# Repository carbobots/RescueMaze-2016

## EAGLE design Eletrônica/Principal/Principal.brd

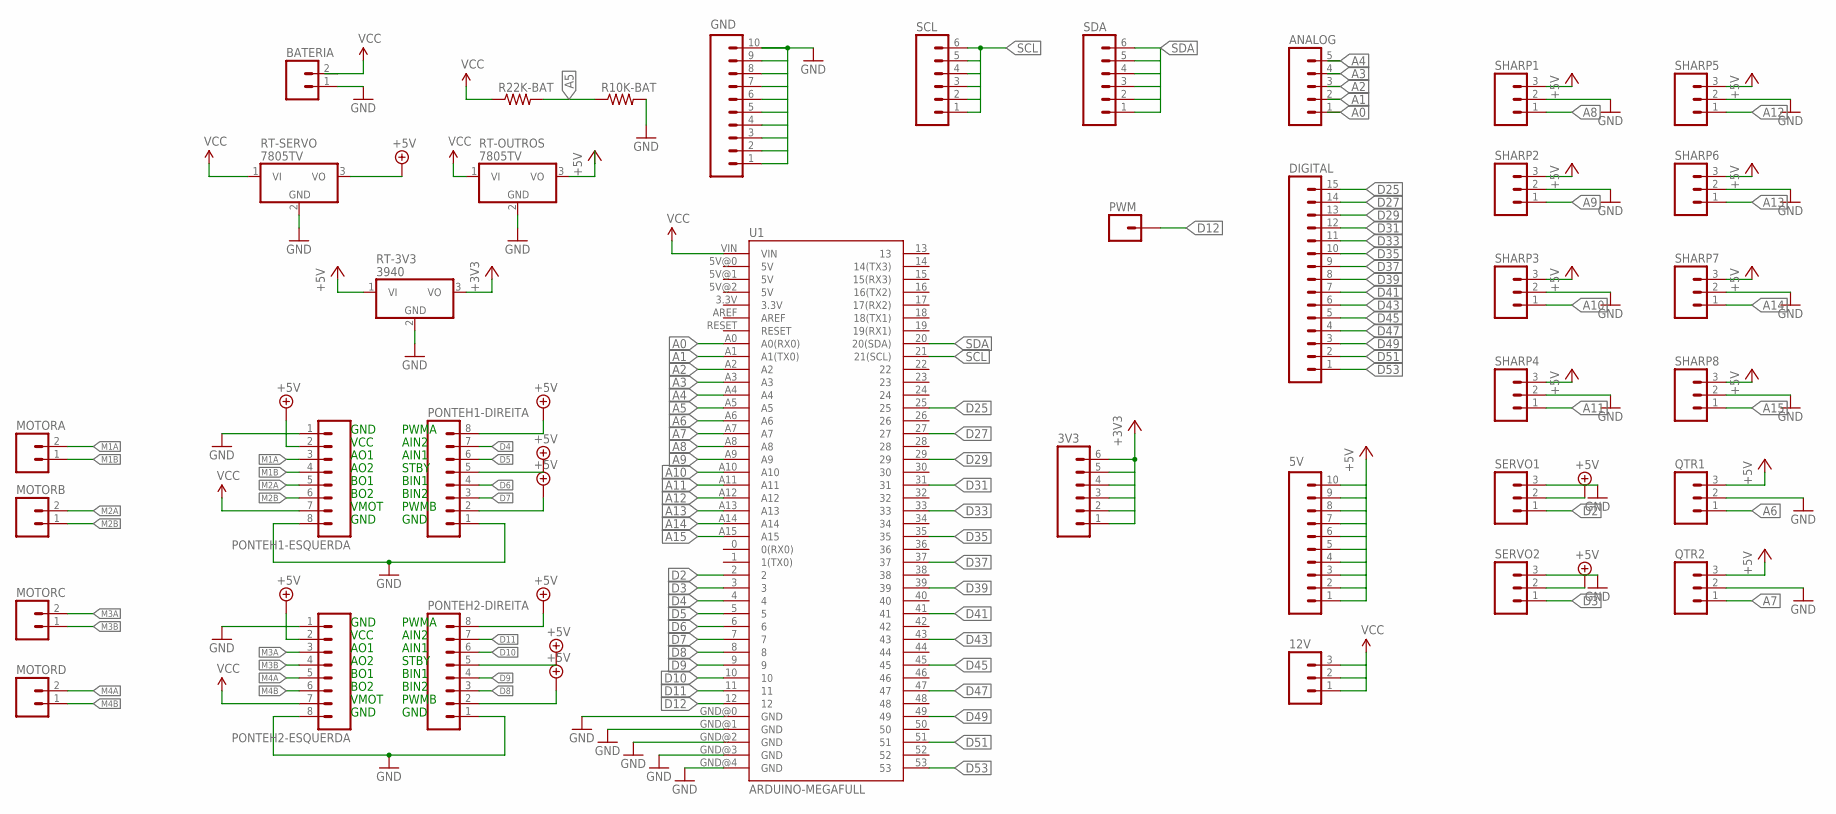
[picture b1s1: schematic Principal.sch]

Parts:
3V3: M06SILK_FEMALE_PTH; 1X06
5V: M10SILK_FEMALE_PTH; 1X10
12V: M03PTH; 1X03
ANALOG: M05PTH; 1X05
BATERIA: M02PTH; 1X02
DIGITAL: M15; 1X15
GND: M10SILK_FEMALE_PTH; 1X10
MOTORA: M02PTH; 1X02
MOTORB: M02PTH; 1X02
MOTORC: M02PTH; 1X02
MOTORD: M02PTH; 1X02
PONTEH1-DIREITA, PONTEH1-ESQUERDA, PONTEH2-DIREITA, PONTEH2-ESQUERDA: M08; 1X08_ROUND
PWM: M01PTH; 1X01
QTR1, QTR2: M03PTH; 1X03
R10K-BAT, R22K-BAT: RESISTORPTH-1/4W; AXIAL-0.4
RT-3V3: 3940; TO220V
RT-OUTROS: 7805TV; TO220V
RT-SERVO: 7805TV; TO220V
SCL: M06SILK_FEMALE_PTH; 1X06
SDA: M06SILK_FEMALE_PTH; 1X06
SERVO1, SERVO2: M03PTH; 1X03
SHARP1, SHARP2, SHARP3, SHARP4, SHARP5, SHARP6, SHARP7, SHARP8: M03PTH; 1X03
U1: ARDUINO-MEGAFULL; ARDUINO_MEGA

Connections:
3V3: 3V3.2, 3V3.3, 3V3.4, 3V3.5, RT-3V3.3 (VO)
5V: 5V.2, 5V.3, 5V.4, 5V.5, 5V.6, 5V.7, 5V.8, 5V.9, 5V.10, RT-OUTROS.3 (VO)
+3V3: 3V3.1, 3V3.6
+5V: 5V.1, PONTEH1-DIREITA.2, PONTEH1-DIREITA.5, PONTEH1-DIREITA.8, PONTEH1-ESQUERDA.2, PONTEH2-DIREITA.2, PONTEH2-DIREITA.5, PONTEH2-DIREITA.8, PONTEH2-ESQUERDA.2, QTR1.3, QTR2.3, RT-3V3.1 (VI), RT-SERVO.3 (VO), SERVO1.2, SERVO2.2, SHARP1.3, SHARP2.3, SHARP3.3, SHARP4.3, SHARP5.3, SHARP6.3, SHARP7.3, SHARP8.3
A0: ANALOG.1, U1.A0 (A0(RX0))
A1: ANALOG.2, U1.A1 (A1(TX0))
A2: ANALOG.3, U1.A2
A3: ANALOG.4, U1.A3
A4: ANALOG.5, U1.A4
A5: R10K-BAT.P$1 (1), R22K-BAT.P$2 (2), U1.A5
A6: QTR1.1, U1.A6
A7: QTR2.1, U1.A7
A8: SHARP1.1, U1.A8
A9: SHARP2.1, U1.A9
A10: SHARP3.1, U1.A10
A11: SHARP4.1, U1.A11
A12: SHARP5.1, U1.A12
A13: SHARP6.1, U1.A13
A14: SHARP7.1, U1.A14
A15: SHARP8.1, U1.A15
D2: SERVO1.1, U1.2
D3: SERVO2.1, U1.3
D4: PONTEH1-DIREITA.7, U1.4
D5: PONTEH1-DIREITA.6, U1.5
D6: PONTEH1-DIREITA.4, U1.6
D7: PONTEH1-DIREITA.3, U1.7
D8: PONTEH2-DIREITA.3, U1.8
D9: PONTEH2-DIREITA.4, U1.9
D10: PONTEH2-DIREITA.6, U1.10
D11: PONTEH2-DIREITA.7, U1.11
D12: PWM.1, U1.12
D25: DIGITAL.15, U1.25
D27: DIGITAL.14, U1.27
D29: DIGITAL.13, U1.29
D31: DIGITAL.12, U1.31
D33: DIGITAL.11, U1.33
D35: DIGITAL.10, U1.35
D37: DIGITAL.9, U1.37
D39: DIGITAL.8, U1.39
D41: DIGITAL.7, U1.41
D43: DIGITAL.6, U1.43
D45: DIGITAL.5, U1.45
D47: DIGITAL.4, U1.47
D49: DIGITAL.3, U1.49
D51: DIGITAL.2, U1.51
D53: DIGITAL.1, U1.53
GND: BATERIA.1, GND.1, GND.10, PONTEH1-DIREITA.1, PONTEH1-ESQUERDA.1, PONTEH1-ESQUERDA.8, PONTEH2-DIREITA.1, PONTEH2-ESQUERDA.1, PONTEH2-ESQUERDA.8, QTR1.2, QTR2.2, R10K-BAT.P$2 (2), RT-3V3.2 (GND), RT-OUTROS.2 (GND), RT-SERVO.2 (GND), SERVO1.3, SERVO2.3, SHARP1.2, SHARP2.2, SHARP3.2, SHARP4.2, SHARP5.2, SHARP6.2, SHARP7.2, SHARP8.2, U1.GND@0 (GND), U1.GND@1 (GND), U1.GND@2 (GND), U1.GND@3 (GND), U1.GND@4 (GND)
M1A: MOTORA.2, PONTEH1-ESQUERDA.3
M1B: MOTORA.1, PONTEH1-ESQUERDA.4
M2A: MOTORB.2, PONTEH1-ESQUERDA.5
M2B: MOTORB.1, PONTEH1-ESQUERDA.6
M3A: MOTORC.2, PONTEH2-ESQUERDA.3
M3B: MOTORC.1, PONTEH2-ESQUERDA.4
M4A: MOTORD.2, PONTEH2-ESQUERDA.5
M4B: MOTORD.1, PONTEH2-ESQUERDA.6
SCL: SCL.1, SCL.2, SCL.3, SCL.4, SCL.5, SCL.6, U1.21 (21(SCL))
SDA: SDA.1, SDA.2, SDA.3, SDA.4, SDA.5, SDA.6, U1.20 (20(SDA))
VCC: 12V.1, 12V.2, 12V.3, BATERIA.2, PONTEH1-ESQUERDA.7, PONTEH2-ESQUERDA.7, R22K-BAT.P$1 (1), RT-OUTROS.1 (VI), RT-SERVO.1 (VI), U1.VIN

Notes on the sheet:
GND
VCC
AO1
AO2
BO1
BO2
VMOT
PWMA
AIN2
AIN1
STBY
BIN1
BIN2
PWMB

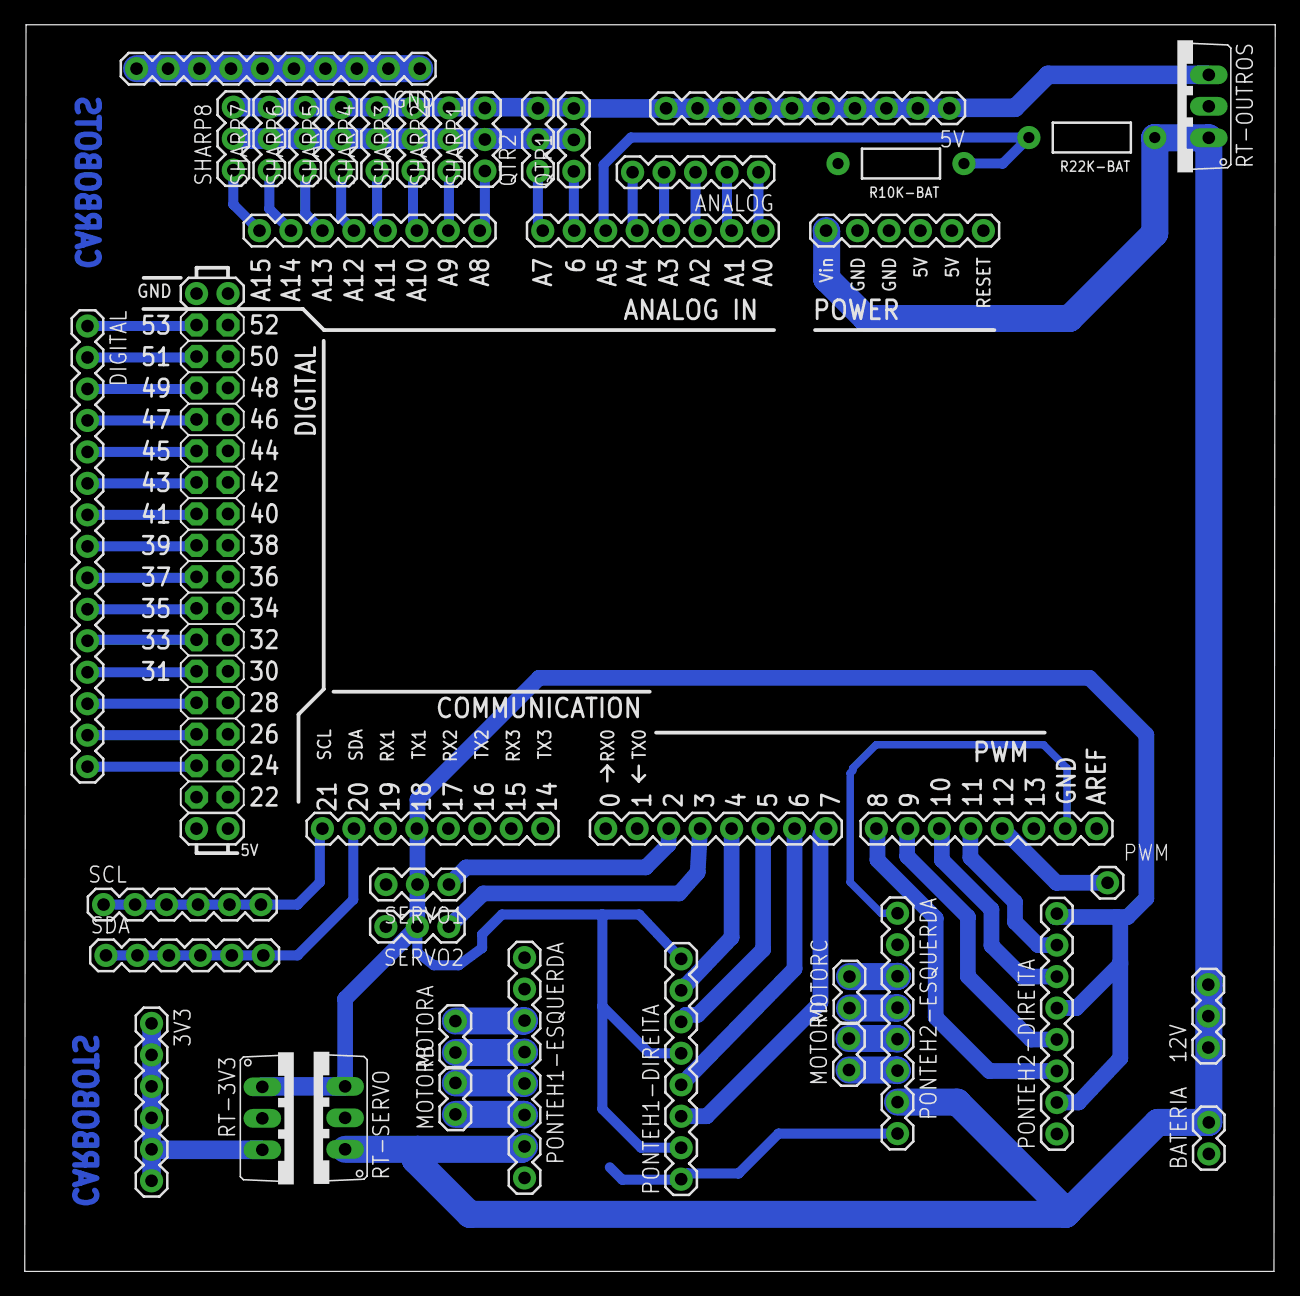
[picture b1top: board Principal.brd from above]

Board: 2 copper layers, 100.9 x 100.6 mm, 36 parts (0 on the bottom side), 58 nets.

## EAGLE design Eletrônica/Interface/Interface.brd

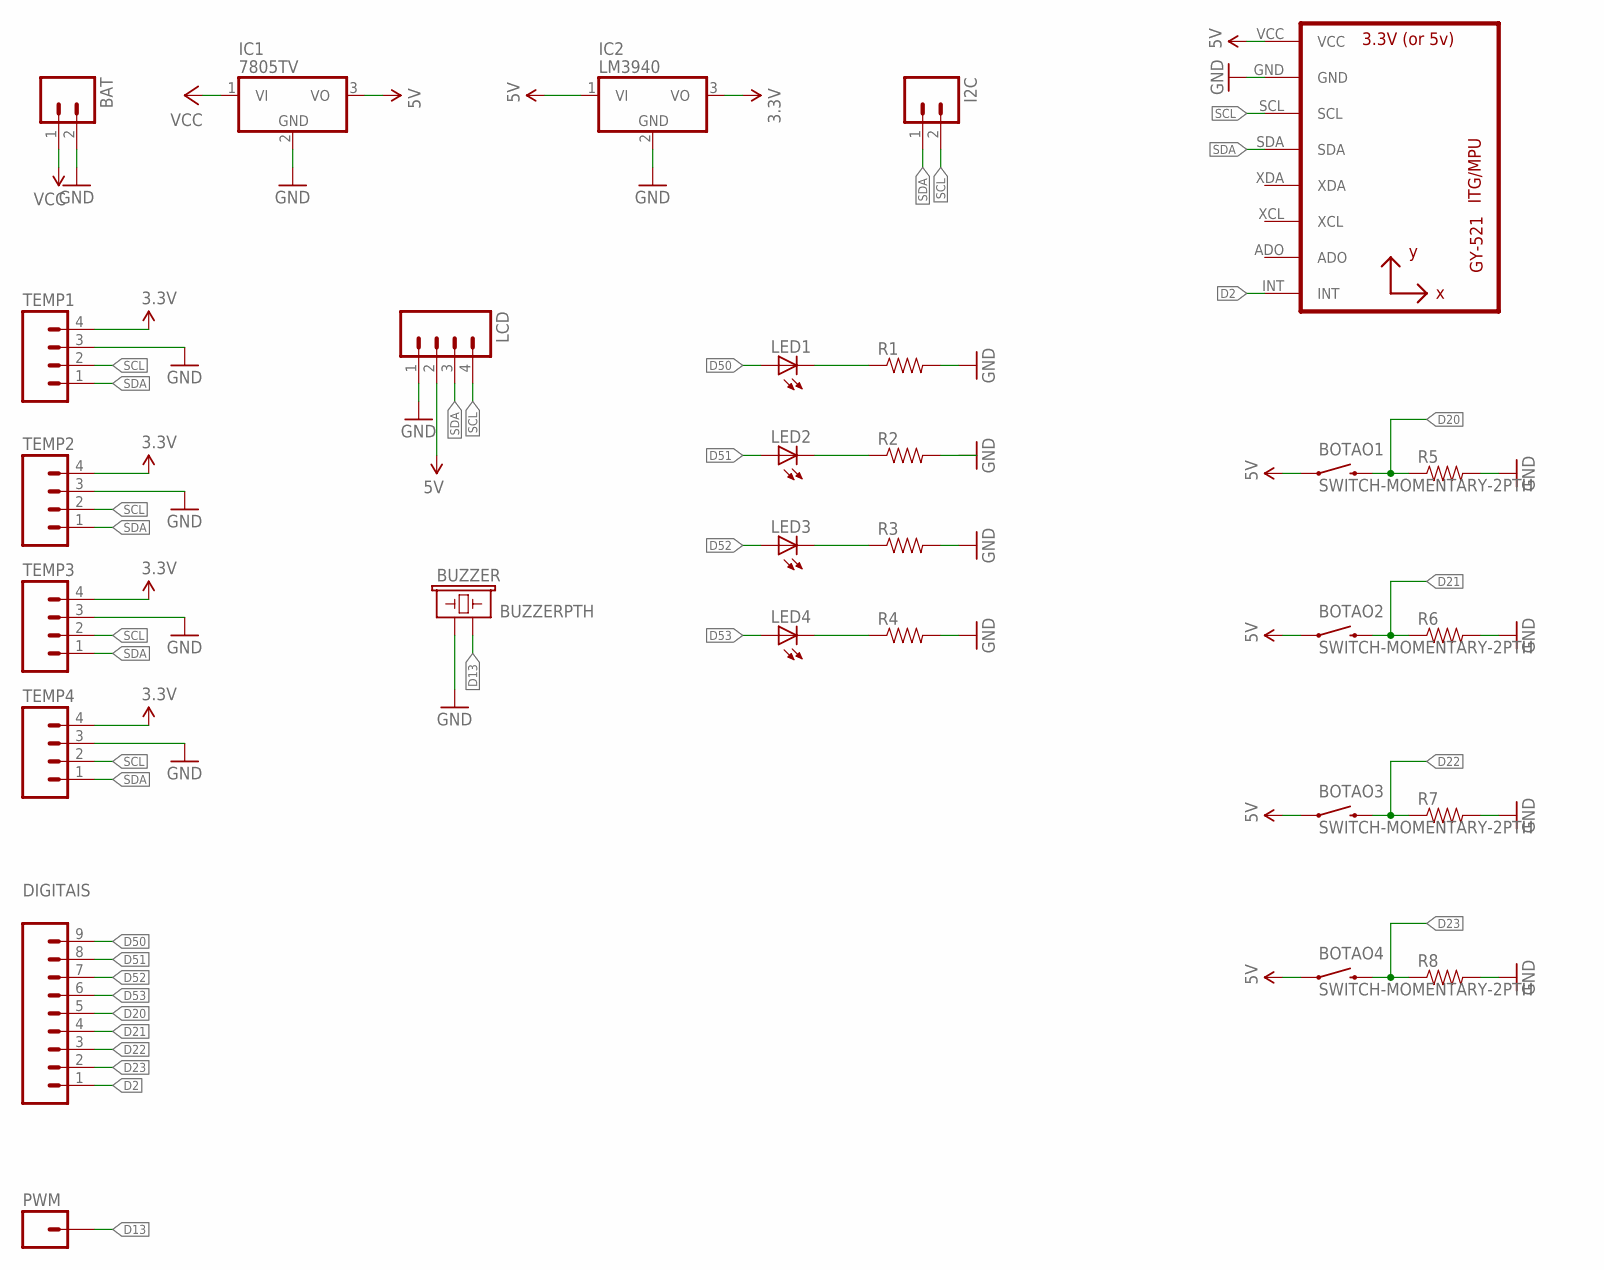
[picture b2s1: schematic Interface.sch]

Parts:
BAT: M02PTH; 1X02
BOTAO1, BOTAO2, BOTAO3, BOTAO4: SWITCH-MOMENTARY-2PTH; TACTILE-PTH
BUZZER: BUZZERPTH; BUZZER-12MM
DIGITAIS: M09; 1X09
I2C: M02PTH; 1X02
IC1: 7805TV; TO220V
IC2: LM3940; TO220V
LCD: M04PTH; 1X04
LED1, LED2, LED3, LED4: LED5MM
PWM: M01PTH; 1X01
R1, R2, R3, R4, R5, R6, R7, R8: RESISTOREZ; AXIAL-0.3EZ
TEMP1, TEMP2, TEMP3, TEMP4: M04PTH; 1X04
U1: GY-521MPU6050; GY-521

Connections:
3.3V: IC2.3 (VO), TEMP1.4, TEMP2.4, TEMP3.4, TEMP4.4
5V: BOTAO1.1, BOTAO2.1, BOTAO3.1, BOTAO4.1, IC1.3 (VO), IC2.1 (VI), LCD.2, U1.VCC
D2: DIGITAIS.1, U1.INT
D13: BUZZER.- (2), PWM.1
D20: BOTAO1.3 (2), DIGITAIS.5, R5.P$1 (1)
D21: BOTAO2.3 (2), DIGITAIS.4, R6.P$1 (1)
D22: BOTAO3.3 (2), DIGITAIS.3, R7.P$1 (1)
D23: BOTAO4.3 (2), DIGITAIS.2, R8.P$1 (1)
D50: DIGITAIS.9, LED1.A
D51: DIGITAIS.8, LED2.A
D52: DIGITAIS.7, LED3.A
D53: DIGITAIS.6, LED4.A
GND: BAT.2, BUZZER.+ (1), IC1.2 (GND), IC2.2 (GND), LCD.1, R1.P$2 (2), R2.P$2 (2), R3.P$2 (2), R4.P$2 (2), R5.P$2 (2), R6.P$2 (2), R7.P$2 (2), R8.P$2 (2), TEMP1.3, TEMP2.3, TEMP3.3, TEMP4.3, U1.GND
unnamed: LED3.K (C), R3.P$1 (1)
unnamed: LED1.K (C), R1.P$1 (1)
unnamed: LED2.K (C), R2.P$1 (1)
unnamed: LED4.K (C), R4.P$1 (1)
SCL: I2C.2, LCD.4, TEMP1.2, TEMP2.2, TEMP3.2, TEMP4.2, U1.SCL
SDA: I2C.1, LCD.3, TEMP1.1, TEMP2.1, TEMP3.1, TEMP4.1, U1.SDA
VCC: BAT.1, IC1.1 (VI)

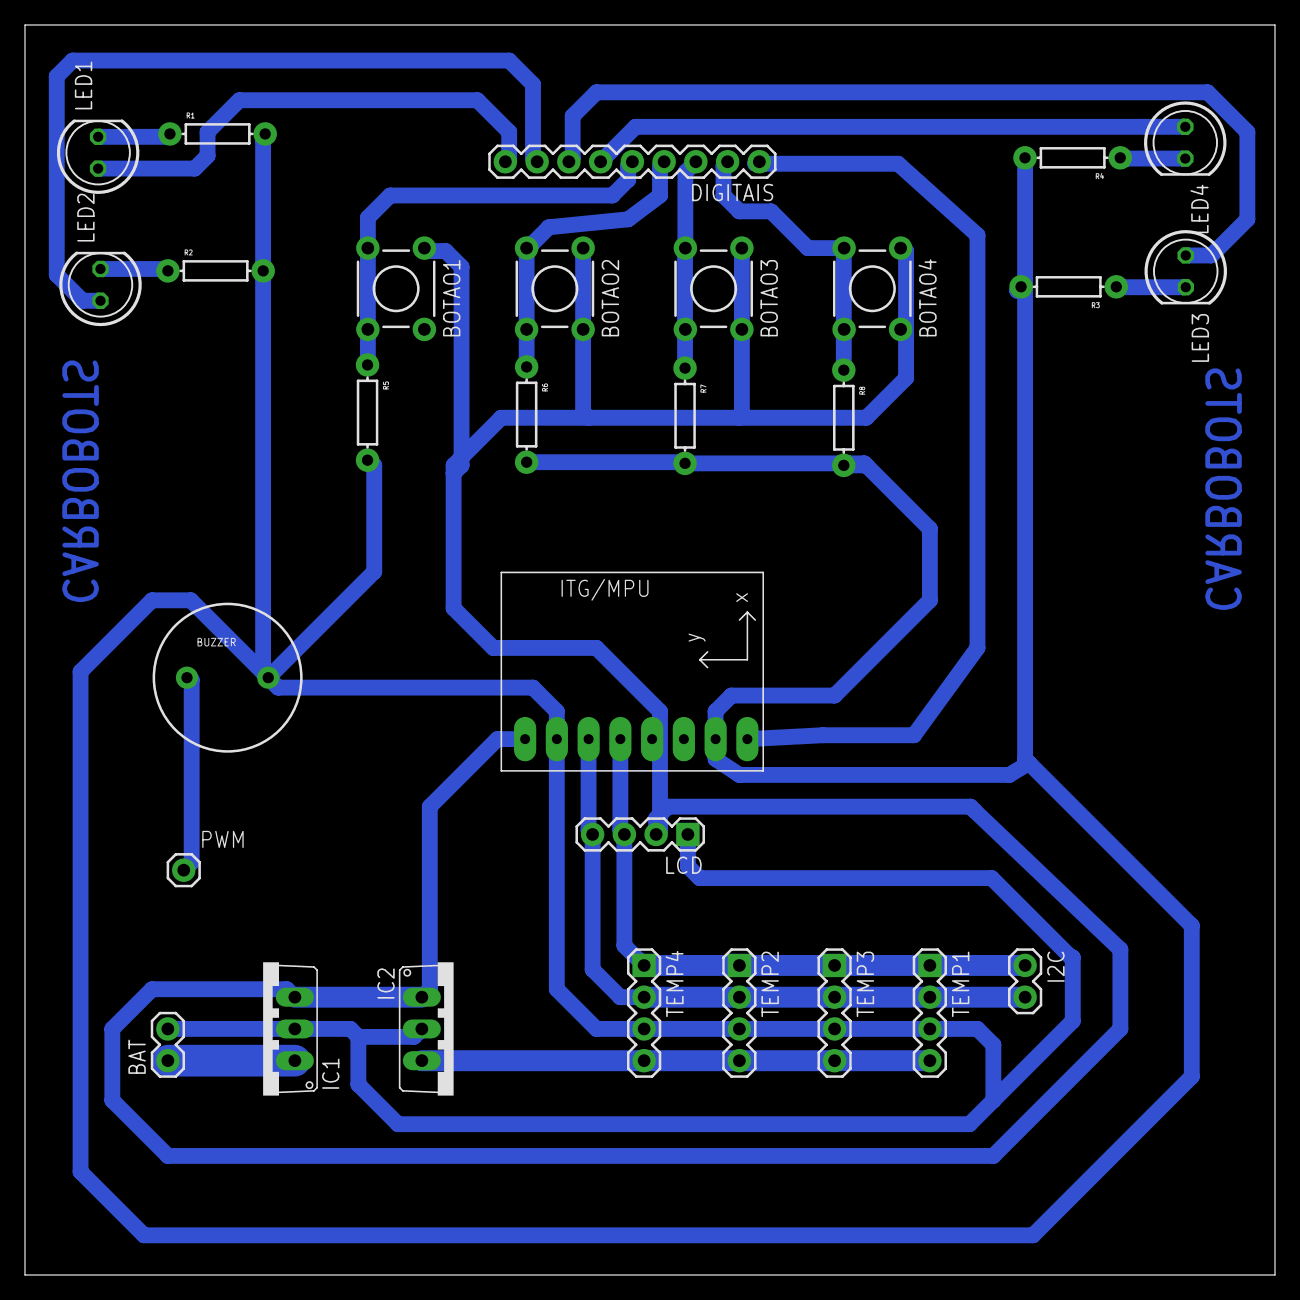
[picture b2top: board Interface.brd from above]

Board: 2 copper layers, 100.0 x 100.0 mm, 29 parts (0 on the bottom side), 20 nets.

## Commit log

2017-05-22 Rescue Maze 2016

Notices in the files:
parts and their libraries:
SparkFun-Connectors: Licensing: Creative Commons ShareAlike 4.0 International - https://creativecommons.org/licenses/by-sa/4.0
